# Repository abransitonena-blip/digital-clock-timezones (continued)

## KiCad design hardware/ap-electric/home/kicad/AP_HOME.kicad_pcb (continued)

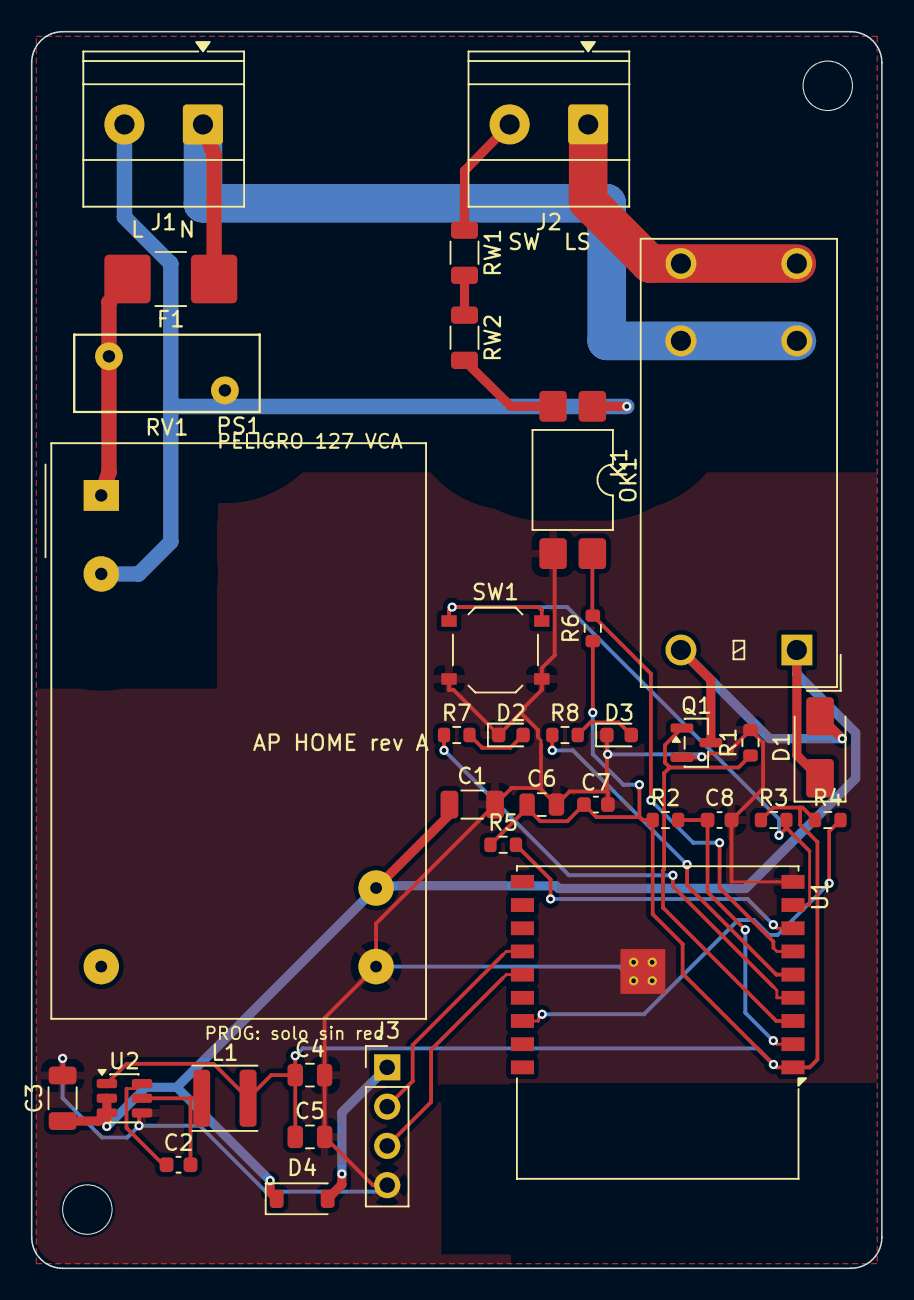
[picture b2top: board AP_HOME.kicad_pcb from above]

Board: 2 copper layers, 55.0 x 80.0 mm, 37 parts (0 on the bottom side), 26 nets.

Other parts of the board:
H1, H2: MountingHole_3.2mm_M3

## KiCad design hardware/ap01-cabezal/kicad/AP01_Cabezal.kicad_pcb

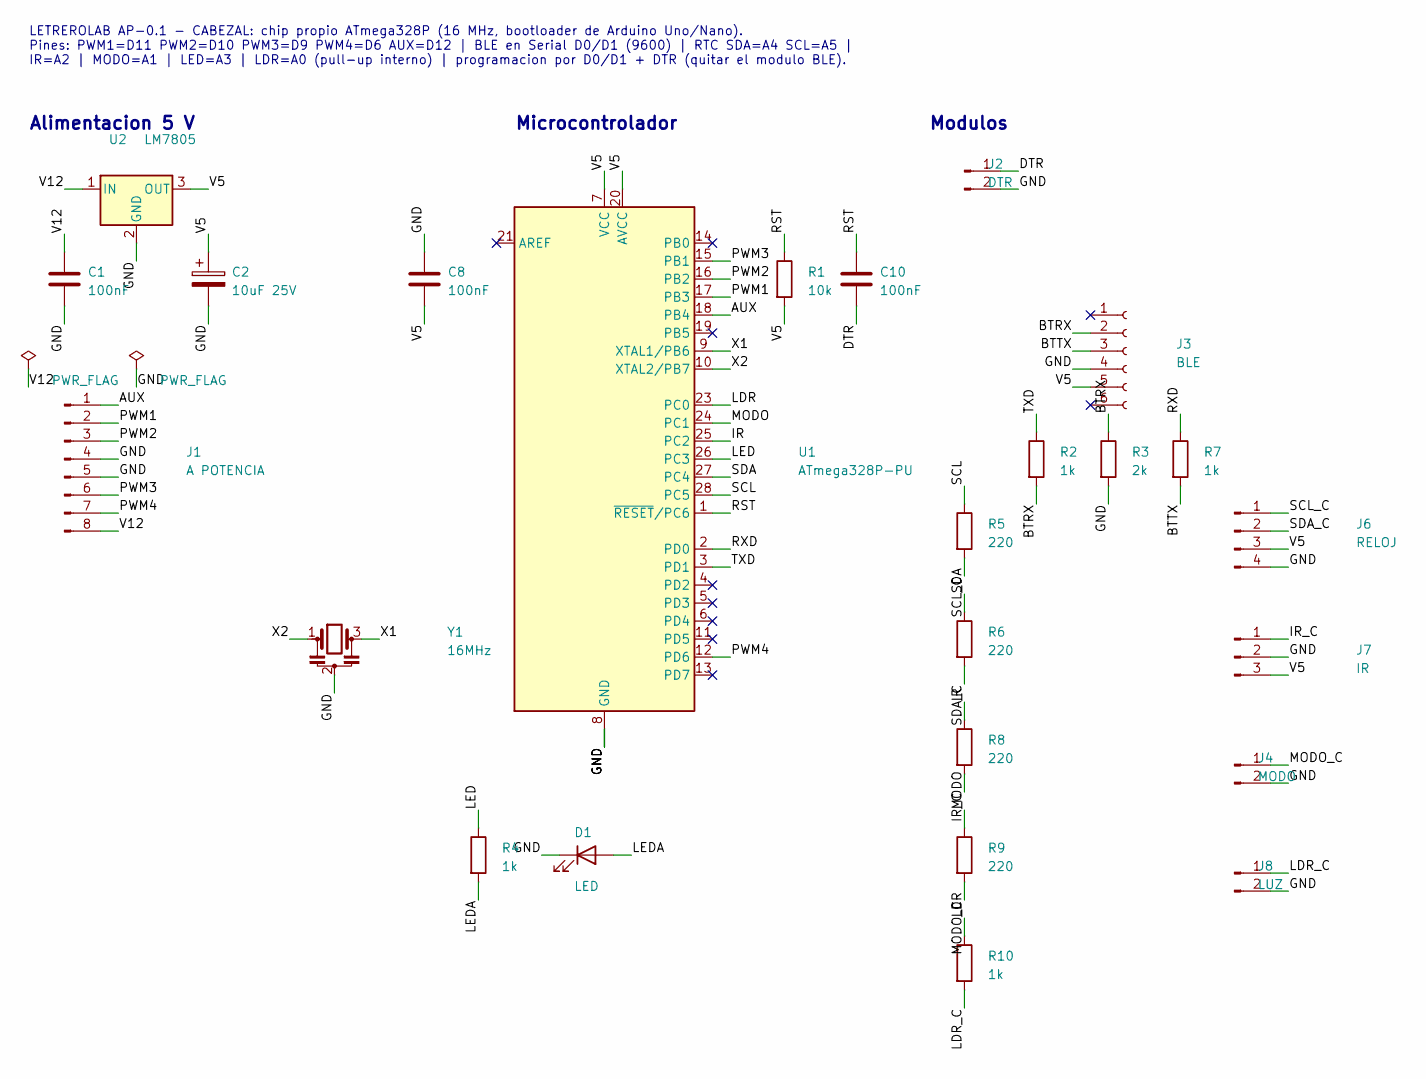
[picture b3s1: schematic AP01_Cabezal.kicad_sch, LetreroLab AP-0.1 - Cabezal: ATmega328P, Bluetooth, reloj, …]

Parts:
C1, C8: 100nF; C_Disc_P2.54mm
C2: 10uF 25V; CP_Radial_D5.0mm_P2.54mm
C10: 100nF; C_Disc_P5.08mm
D1: LED; LED_D3.0mm
J1: A POTENCIA; Pines_1x08_P2.54mm
J2: DTR; Pines_1x02_P2.54mm
J3: BLE; Zocalo_1x06_P2.54mm
J4: MODO; Pines_1x02_P2.54mm
J6: RELOJ; Pines_1x04_P2.54mm
J7: IR; Pines_1x03_P2.54mm
J8: LUZ; Pines_1x02_P2.54mm
R1: 10k; R_Vertical_P2.54mm
R2, R4, R7, R10: 1k; R_Vertical_P5.08mm
R3: 2k; R_Vertical_P5.08mm
R5, R6, R8, R9: 220; R_Vertical_P5.08mm
U1: ATmega328P-PU; DIP-28_W7.62mm
U2: LM7805; TO-220_7805
Y1: 16MHz; Resonador_3P_P2.54mm

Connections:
/AUX: J1.1, U1.18 (PB4)
/BTRX: J3.2, R2.2, R3.1
/BTTX: J3.3, R7.2
/DTR: C10.2, J2.1
/GND: C1.2, C2.2, C8.1, D1.1 (K), J1.4, J1.5, J2.2, J3.4, J4.2, J6.4, J7.2, J8.2, R3.2, U1.8 (GND), U1.22 (GND), U2.2 (GND), Y1.2
/IR: R8.1, U1.25 (PC2)
/IR_C: J7.1, R8.2
/LDR: R10.1, U1.23 (PC0)
/LDR_C: J8.1, R10.2
/LED: R4.1, U1.26 (PC3)
/LEDA: D1.2 (A), R4.2
/MODO: R9.1, U1.24 (PC1)
/MODO_C: J4.1, R9.2
/PWM1: J1.2, U1.17 (PB3)
/PWM2: J1.3, U1.16 (PB2)
/PWM3: J1.6, U1.15 (PB1)
/PWM4: J1.7, U1.12 (PD6)
/RST: C10.1, R1.1, U1.1 (~RESET/PC6)
/RXD: R7.1, U1.2 (PD0)
/SCL: R5.1, U1.28 (PC5)
/SCL_C: J6.1, R5.2
/SDA: R6.1, U1.27 (PC4)
/SDA_C: J6.2, R6.2
/TXD: R2.1, U1.3 (PD1)
/V5: C2.1, C8.2, J3.5, J6.3, J7.3, R1.2, U1.7 (VCC), U1.20 (AVCC), U2.3 (OUT)
/V12: C1.1, J1.8, U2.1 (IN)
/X1: U1.9 (XTAL1/PB6), Y1.3
/X2: U1.10 (XTAL2/PB7), Y1.1

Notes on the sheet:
LETREROLAB AP-0.1 - CABEZAL: chip propio ATmega328P (16 MHz, bootloader de Arduino Uno/Nano). Pines: PWM1=D11 PWM2=D10 PWM3=D9 PWM4=D6 AUX=D12 | BLE en Serial D0/D1 (9600) | RTC SDA=A4 SCL=A5 | IR=A2 | MODO=A1 | LED=A3 | LDR=A0 (pull-up interno) | programacion por D0/D1 + DTR (quitar el modulo BLE).
Alimentacion 5 V
Microcontrolador
Modulos

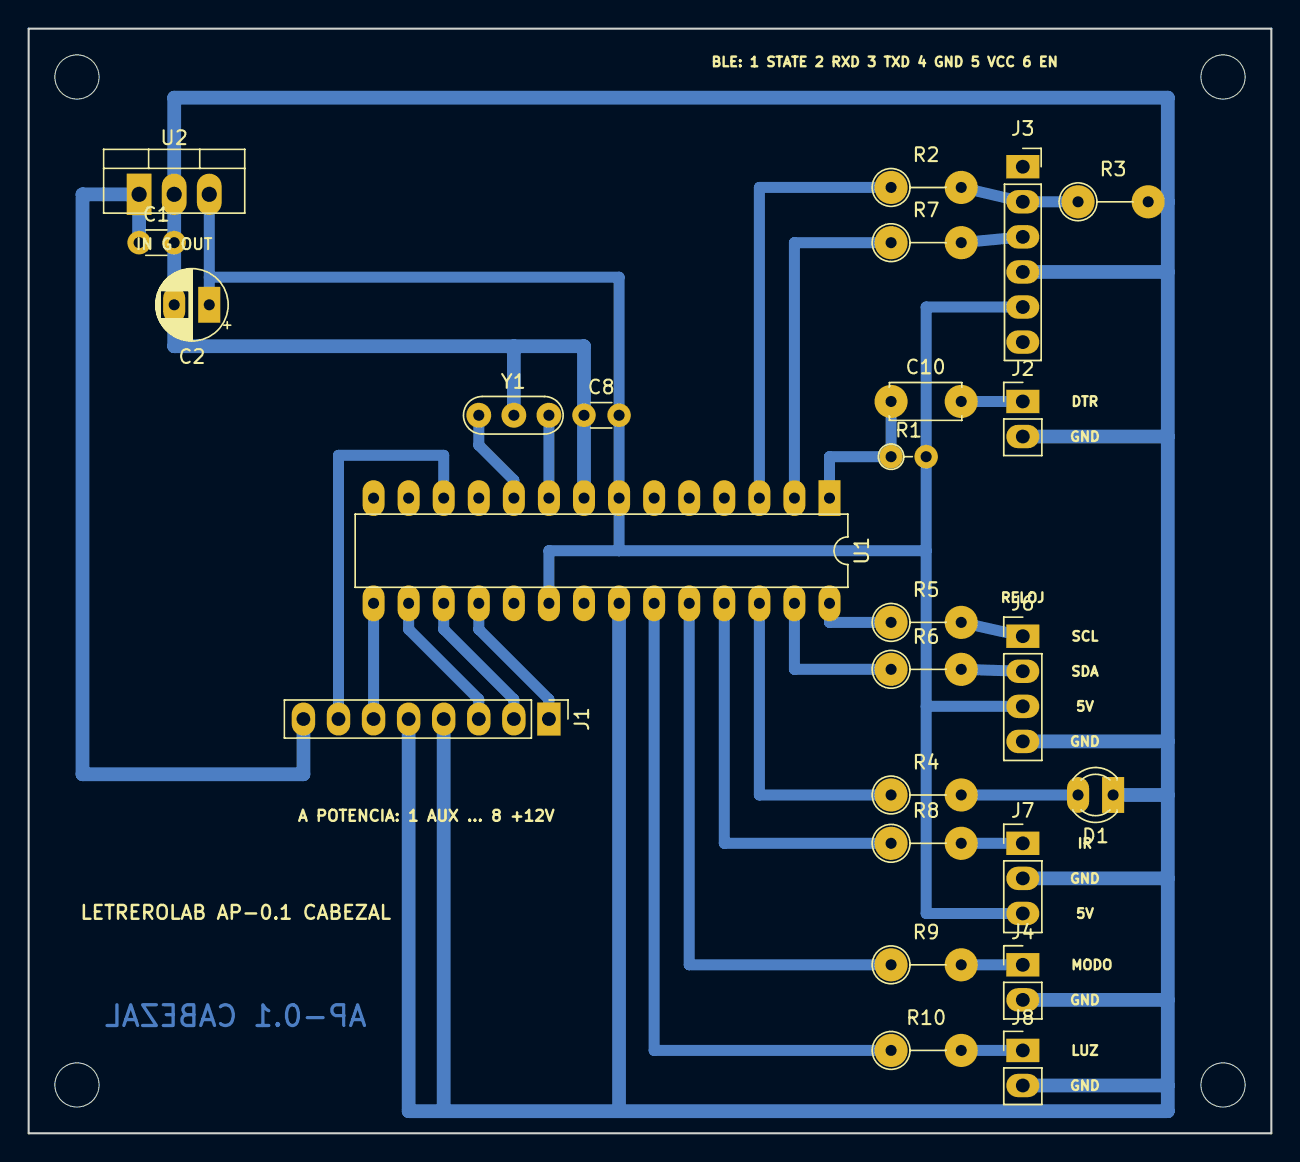
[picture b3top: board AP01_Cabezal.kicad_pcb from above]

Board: 2 copper layers, 90.0 x 80.0 mm, 29 parts (0 on the bottom side), 28 nets.

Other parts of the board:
H1, H2, H3, H4: MountingHole_3.2mm_M3; Barreno_M3_3.2mm

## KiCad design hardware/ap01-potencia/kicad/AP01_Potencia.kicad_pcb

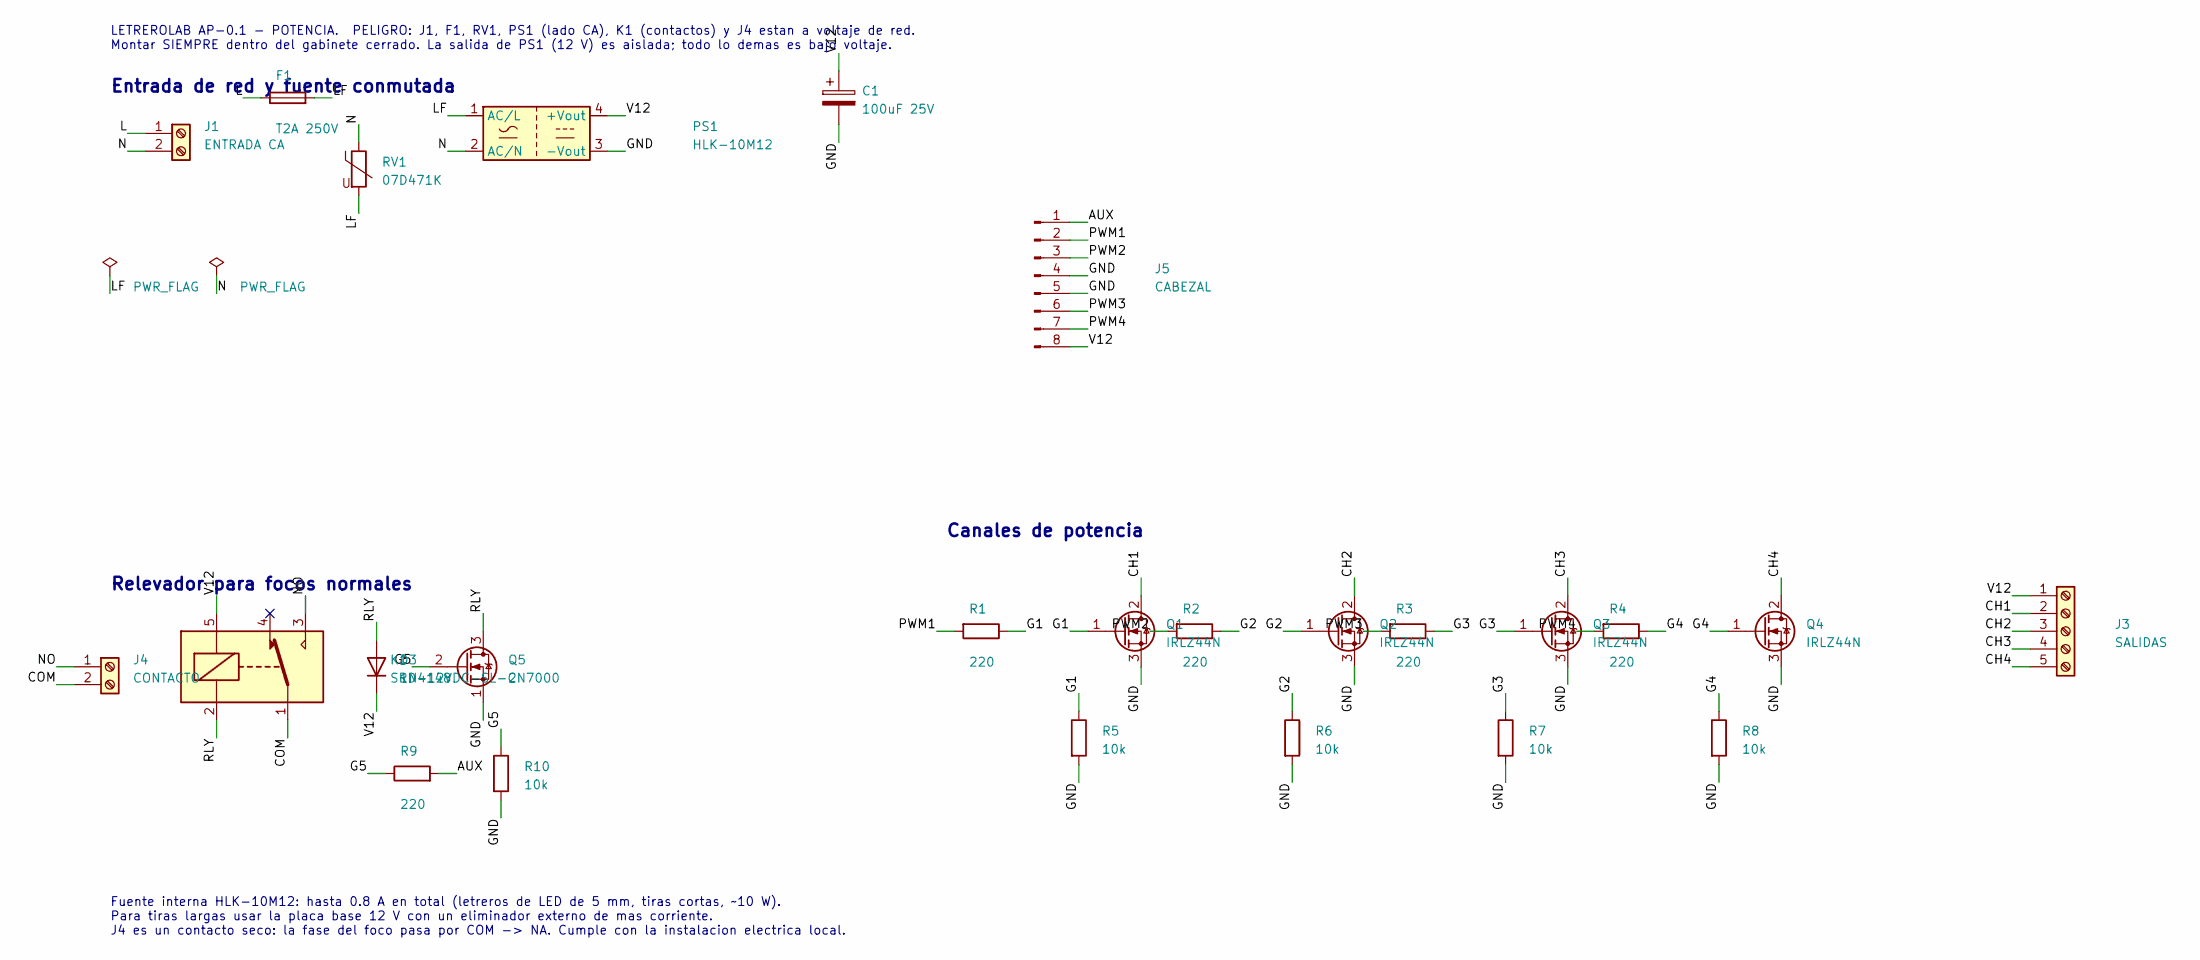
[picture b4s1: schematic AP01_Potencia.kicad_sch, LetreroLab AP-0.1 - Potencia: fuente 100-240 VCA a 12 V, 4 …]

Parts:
C1: 100uF 25V; CP_Radial_D5.0mm_P2.54mm
D3: 1N4148; D_DO-35_Vertical_P5.08mm
F1: T2A 250V; Fusible_TR5_P5.08mm
J1: ENTRADA CA; Clema_2P_P5.08mm
J3: SALIDAS; Clema_5P_P5.08mm
J4: CONTACTO; Clema_2P_P5.08mm
J5: CABEZAL; Pines_1x08_P2.54mm
K1: SRD-12VDC-SL-C; Rele_SRD_FormC
PS1: HLK-10M12; HLK-10Mxx
Q1, Q2, Q3, Q4: IRLZ44N; TO-220_MOSFET
Q5: 2N7000; TO-92_2N7000
R1, R2, R3, R4, R9: 220; R_Vertical_P5.08mm
R5, R6, R7, R8: 10k; R_Vertical_P5.08mm
R10: 10k; R_Vertical_P2.54mm
RV1: 07D471K; Varistor_D7mm_P5mm

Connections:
/AUX: J5.1, R9.2
/CH1: J3.2, Q1.2 (D)
/CH2: J3.3, Q2.2 (D)
/CH3: J3.4, Q3.2 (D)
/CH4: J3.5, Q4.2 (D)
/COM: J4.2, K1.1
/G1: Q1.1 (G), R1.1, R5.1
/G2: Q2.1 (G), R2.1, R6.1
/G3: Q3.1 (G), R3.1, R7.1
/G4: Q4.1 (G), R4.1, R8.1
/G5: Q5.2 (G), R9.1, R10.1
/GND: C1.2, J5.4, J5.5, PS1.3 (-Vout), Q1.3 (S), Q2.3 (S), Q3.3 (S), Q4.3 (S), Q5.1 (S), R5.2, R6.2, R7.2, R8.2, R10.2
/L: F1.1, J1.1
/LF: F1.2, PS1.1 (AC/L), RV1.2
/N: J1.2, PS1.2 (AC/N), RV1.1
/NO: J4.1, K1.3
/PWM1: J5.2, R1.2
/PWM2: J5.3, R2.2
/PWM3: J5.6, R3.2
/PWM4: J5.7, R4.2
/RLY: D3.2 (A), K1.2, Q5.3 (D)
/V12: C1.1, D3.1 (K), J3.1, J5.8, K1.5, PS1.4 (+Vout)

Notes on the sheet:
LETREROLAB AP-0.1 - POTENCIA. PELIGRO: J1, F1, RV1, PS1 (lado CA), K1 (contactos) y J4 estan a voltaje de red. Montar SIEMPRE dentro del gabinete cerrado. La salida de PS1 (12 V) es aislada; todo lo demas es bajo voltaje.
Fuente interna HLK-10M12: hasta 0.8 A en total (letreros de LED de 5 mm, tiras cortas, ~10 W). Para tiras largas usar la placa base 12 V con un eliminador externo de mas corriente. J4 es un contacto seco: la fase del foco pasa por COM -> NA. Cumple con la instalacion electrica local.
Entrada de red y fuente conmutada
Relevador para focos normales
Canales de potencia

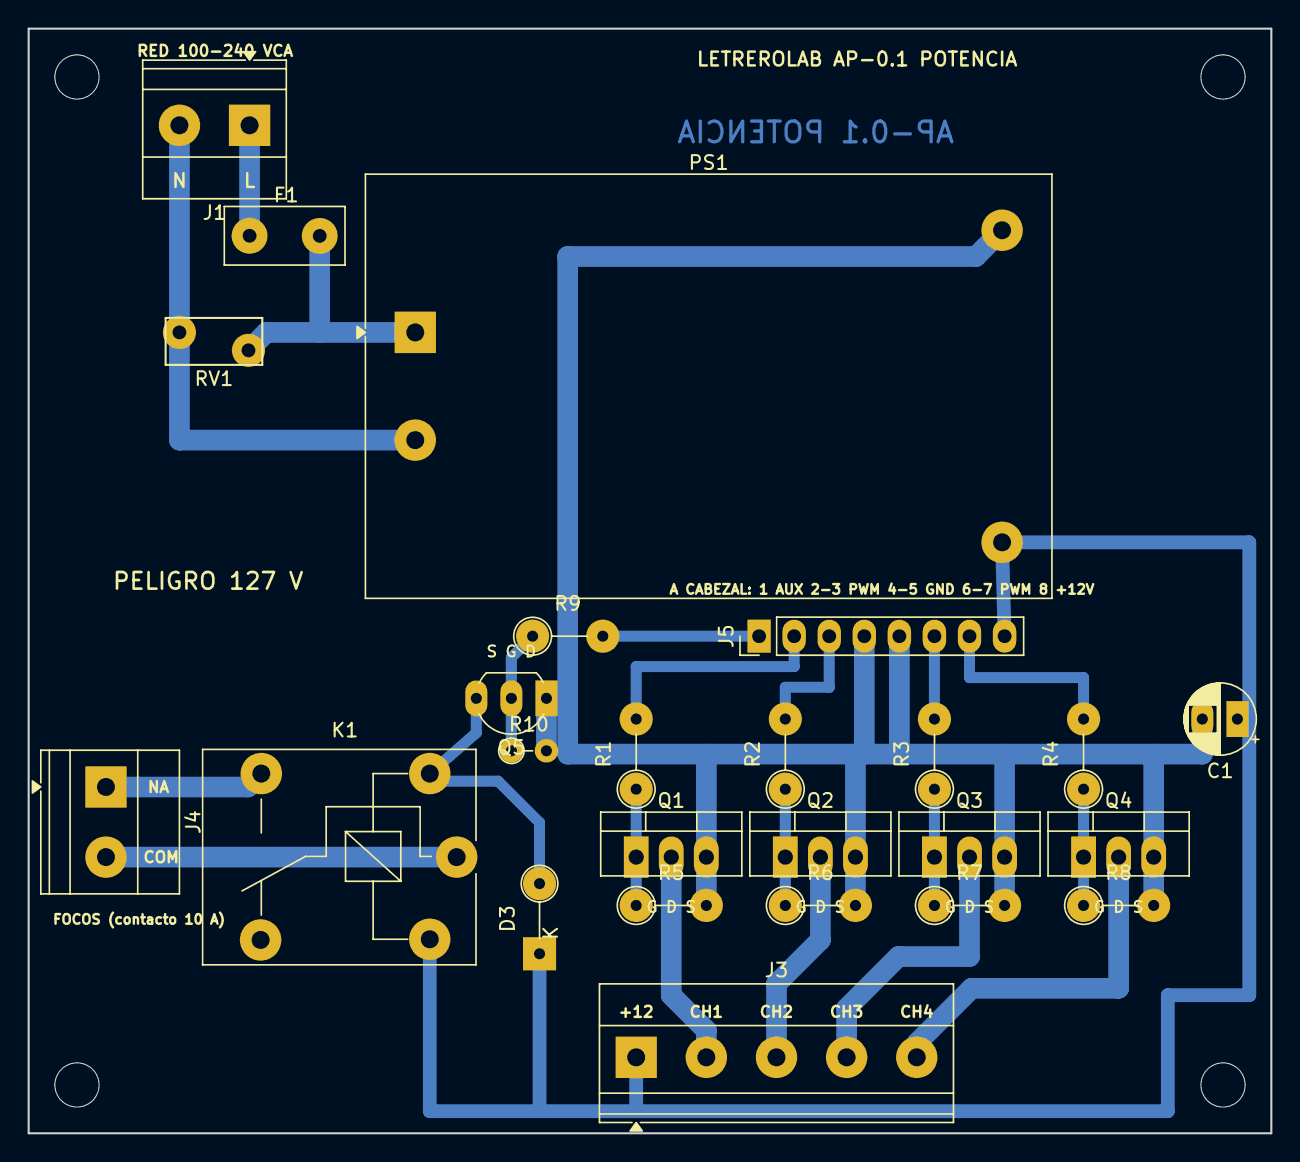
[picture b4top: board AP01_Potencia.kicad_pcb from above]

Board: 2 copper layers, 90.0 x 80.0 mm, 29 parts (0 on the bottom side), 22 nets.

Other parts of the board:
H1, H2, H3, H4: MountingHole_3.2mm_M3; Barreno_M3_3.2mm

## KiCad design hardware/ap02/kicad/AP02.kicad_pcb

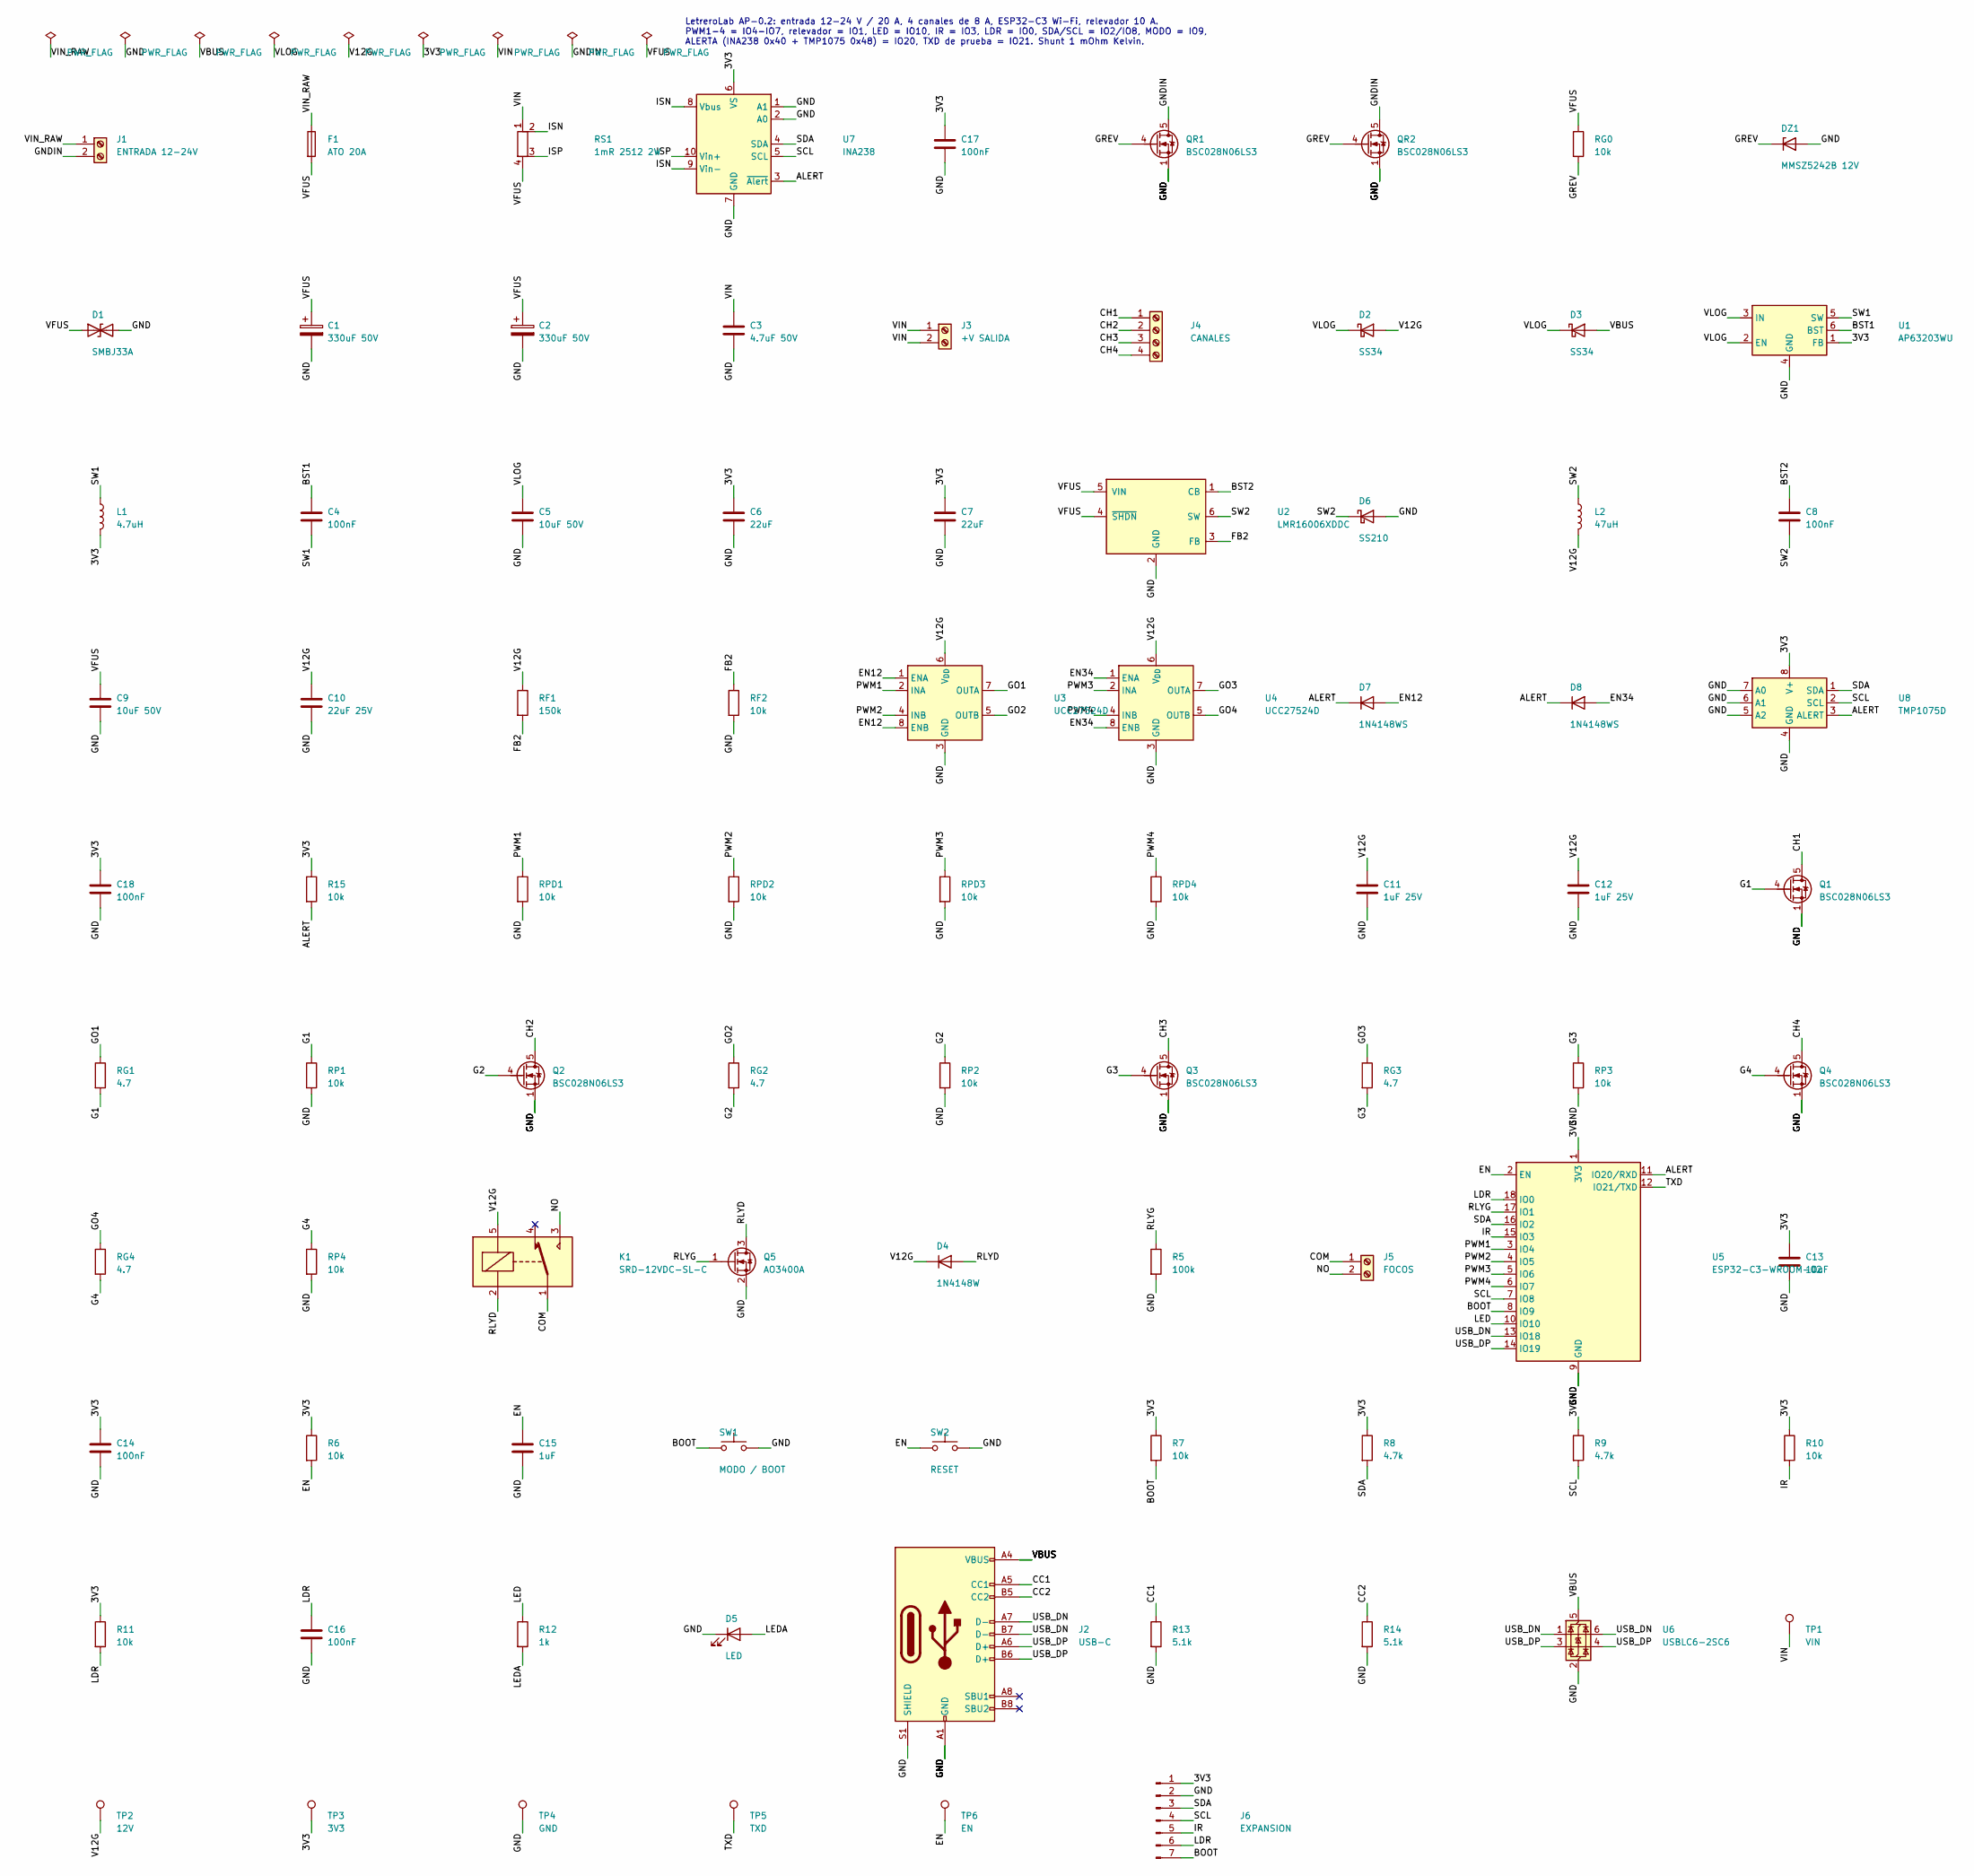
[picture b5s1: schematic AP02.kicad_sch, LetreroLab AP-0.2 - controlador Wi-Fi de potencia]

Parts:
C1, C2: 330uF 50V; CP_Elec_10x10.5
C3: 4.7uF 50V; C_1206_3216Metric
C4, C8, C14, C16, C17, C18: 100nF; C_0603_1608Metric
C5, C9: 10uF 50V; C_1206_3216Metric
C6, C7: 22uF; C_0805_2012Metric
C10: 22uF 25V; C_1206_3216Metric
C11, C12: 1uF 25V; C_0603_1608Metric
C13: 10uF; C_0805_2012Metric
C15: 1uF; C_0603_1608Metric
D1: SMBJ33A; D_SMB
D2, D3: SS34; D_SMA
D4: 1N4148W; D_SOD-123
D5: LED; LED_0603_1608Metric
D6: SS210; D_SMA
D7, D8: 1N4148WS; D_SOD-323
DZ1: MMSZ5242B 12V; D_SOD-123
F1: ATO 20A; Fuseholder_Blade_ATO_Littelfuse_Pudenz_2_Pin
J1: ENTRADA 12-24V; TerminalBlock_Phoenix_MKDS-3-2-5.08_1x02_P5.08mm_Horizontal
J2: USB-C; USB_C_Receptacle_HRO_TYPE-C-31-M-12
J3: +V SALIDA; TerminalBlock_Phoenix_MKDS-3-2-5.08_1x02_P5.08mm_Horizontal
J4: CANALES; TerminalBlock_Phoenix_MKDS-3-4-5.08_1x04_P5.08mm_Horizontal
J5: FOCOS; TerminalBlock_Phoenix_MKDS-1,5-2-5.08_1x02_P5.08mm_Horizont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
J6: EXPANSION; PinHeader_1x07_P2.54mm_Vertical
K1: SRD-12VDC-SL-C; Relay_SPDT_SANYOU_SRD_Series_Form_C
L1: 4.7uH; L_Changjiang_FNR4030S
L2: 47uH; L_Changjiang_FNR4030S
Q1, Q2, Q3, Q4: BSC028N06LS3; TDSON-8-1
Q5: AO3400A; SOT-23
QR1, QR2: BSC028N06LS3; TDSON-8-1
R5: 100k; R_0603_1608Metric
R6, R7, R10, R11, R15: 10k; R_0603_1608Metric
R8, R9: 4.7k; R_0603_1608Metric
R12: 1k; R_0603_1608Metric
R13, R14: 5.1k; R_0603_1608Metric
RF1: 150k; R_0603_1608Metric
RF2: 10k; R_0603_1608Metric
RG0: 10k; R_0603_1608Metric
RG1, RG2, RG3, RG4: 4.7; R_0603_1608Metric
RP1, RP2, RP3, RP4: 10k; R_0603_1608Metric
RPD1, RPD2, RPD3, RPD4: 10k; R_0603_1608Metric
RS1: 1mR 2512 2W; R_2512_Kelvin_NetTie
SW1: MODO / BOOT; SW_Push_1P1T_XKB_TS-1187A
SW2: RESET; SW_Push_1P1T_XKB_TS-1187A
TP1: VIN; TestPoint_Pad_D1.5mm
TP2: 12V; TestPoint_Pad_D1.5mm
TP3: 3V3; TestPoint_Pad_D1.5mm
TP4: GND; TestPoint_Pad_D1.5mm
TP5: TXD; TestPoint_Pad_D1.5mm
TP6: EN; TestPoint_Pad_D1.5mm
U1: AP63203WU; TSOT-23-6
U2: LMR16006XDDC; SOT-23-6
U3, U4: UCC27524D; SOIC-8_3.9x4.9mm_P1.27mm
U5: ESP32-C3-WROOM-02; ESP32-C3-WROOM-02_JLC
U6: USBLC6-2SC6; SOT-23-6
U7: INA238; VSSOP-10_3x3mm_P0.5mm
U8: TMP1075D; SOIC-8_3.9x4.9mm_P1.27mm

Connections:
/3V3: C6.1, C7.1, C13.1, C14.1, C17.1, C18.1, J6.1, L1.2, R6.1, R7.1, R8.1, R9.1, R10.1, R11.1, R15.1, TP3.1, U1.1 (FB), U5.1 (3V3), U7.6 (VS), U8.8 (V+)
/ALERT: D7.1 (K), D8.1 (K), R15.2, U5.11 (IO20/RXD), U7.3 (~Alert), U8.3 (ALERT)
/BOOT: J6.7, R7.2, SW1.1, U5.8 (IO9)
/BST1: C4.1, U1.6 (BST)
/BST2: C8.1, U2.1 (CB)
/CC1: J2.A5 (CC1), R13.1
/CC2: J2.B5 (CC2), R14.1
/CH1: J4.1, Q1.5 (D)
/CH2: J4.2, Q2.5 (D)
/CH3: J4.3, Q3.5 (D)
/CH4: J4.4, Q4.5 (D)
/COM: J5.1, K1.1
/EN: C15.1, R6.2, SW2.1, TP6.1, U5.2 (EN)
/EN12: D7.2 (A), U3.1 (ENA), U3.8 (ENB)
/EN34: D8.2 (A), U4.1 (ENA), U4.8 (ENB)
/FB2: RF1.2, RF2.1, U2.3 (FB)
/G1: Q1.4 (G), RG1.2, RP1.1
/G2: Q2.4 (G), RG2.2, RP2.1
/G3: Q3.4 (G), RG3.2, RP3.1
/G4: Q4.4 (G), RG4.2, RP4.1
/GND: C1.2, C2.2, C3.2, C5.2, C6.2, C7.2, C9.2, C10.2, C11.2, C12.2, C13.2, C14.2, C15.2, C16.2, C17.2, C18.2, D1.2 (A2), D5.1 (K), D6.2 (A), DZ1.2 (A), J2.A1 (GND), J2.A12 (GND), J2.B1 (GND), J2.B12 (GND), J2.S1 (SHIELD), J6.2, Q1.1 (S), Q1.2 (S), Q1.3 (S), Q2.1 (S), Q2.2 (S), Q2.3 (S), Q3.1 (S), Q3.2 (S), Q3.3 (S), Q4.1 (S), Q4.2 (S), Q4.3 (S), Q5.2 (S), QR1.1 (S), QR1.2 (S), QR1.3 (S), QR2.1 (S), QR2.2 (S), QR2.3 (S), R5.2, R13.2, R14.2, RF2.2, RP1.2, RP2.2, RP3.2, RP4.2, RPD1.2, RPD2.2, RPD3.2, RPD4.2, SW1.2, SW2.2, TP4.1, U1.4 (GND), U2.2 (GND), U3.3 (GND), U4.3 (GND), U5.9 (GND), U5.19 (GND), U6.2 (GND), U7.1 (A1), U7.2 (A0), U7.7 (GND), U8.4 (GND), U8.5 (A2), U8.6 (A1), U8.7 (A0)
/GNDIN: J1.2, QR1.5 (D), QR2.5 (D)
/GO1: RG1.1, U3.7 (OUTA)
/GO2: RG2.1, U3.5 (OUTB)
/GO3: RG3.1, U4.7 (OUTA)
/GO4: RG4.1, U4.5 (OUTB)
/GREV: DZ1.1 (K), QR1.4 (G), QR2.4 (G), RG0.2
/IR: J6.5, R10.2, U5.15 (IO3)
/ISN: RS1.2, U7.8 (Vbus), U7.9 (Vin-)
/ISP: RS1.3, U7.10 (Vin+)
/LDR: C16.1, J6.6, R11.2, U5.18 (IO0)
/LED: R12.1, U5.10 (IO10)
/LEDA: D5.2 (A), R12.2
/NO: J5.2, K1.3
/PWM1: RPD1.1, U3.2 (INA), U5.3 (IO4)
/PWM2: RPD2.1, U3.4 (INB), U5.4 (IO5)
/PWM3: RPD3.1, U4.2 (INA), U5.5 (IO6)
/PWM4: RPD4.1, U4.4 (INB), U5.6 (IO7)
/RLYD: D4.2 (A), K1.2, Q5.3 (D)
/RLYG: Q5.1 (G), R5.1, U5.17 (IO1)
/SCL: J6.4, R9.2, U5.7 (IO8), U7.5 (SCL), U8.2 (SCL)
/SDA: J6.3, R8.2, U5.16 (IO2), U7.4 (SDA), U8.1 (SDA)
/SW1: C4.2, L1.1, U1.5 (SW)
/SW2: C8.2, D6.1 (K), L2.1, U2.6 (SW)
/TXD: TP5.1, U5.12 (IO21/TXD)
/USB_DN: J2.A7 (D-), J2.B7 (D-), U5.13 (IO18), U6.1 (I/O1), U6.6 (I/O1)
/USB_DP: J2.A6 (D+), J2.B6 (D+), U5.14 (IO19), U6.3 (I/O2), U6.4 (I/O2)
/V12G: C10.1, C11.1, C12.1, D2.2 (A), D4.1 (K), K1.5, L2.2, RF1.1, TP2.1, U3.6 (V_{DD}), U4.6 (V_{DD})
/VBUS: D3.2 (A), J2.A4 (VBUS), J2.A9 (VBUS), J2.B4 (VBUS), J2.B9 (VBUS), U6.5 (VBUS)
/VFUS: C1.1, C2.1, C9.1, D1.1 (A1), F1.2, RG0.1, RS1.4, U2.4 (~SHDN), U2.5 (VIN)
/VIN: C3.1, J3.1, J3.2, RS1.1, TP1.1
/VIN_RAW: F1.1, J1.1
/VLOG: C5.1, D2.1 (K), D3.1 (K), U1.2 (EN), U1.3 (IN)

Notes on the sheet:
LetreroLab AP-0.2: entrada 12-24 V / 20 A, 4 canales de 8 A, ESP32-C3 Wi-Fi, relevador 10 A. PWM1-4 = IO4-IO7, relevador = IO1, LED = IO10, IR = IO3, LDR = IO0, SDA/SCL = IO2/IO8, MODO = IO9, ALERTA (INA238 0x40 + TMP1075 0x48) = IO20, TXD de prueba = IO21. Shunt 1 mOhm Kelvin.

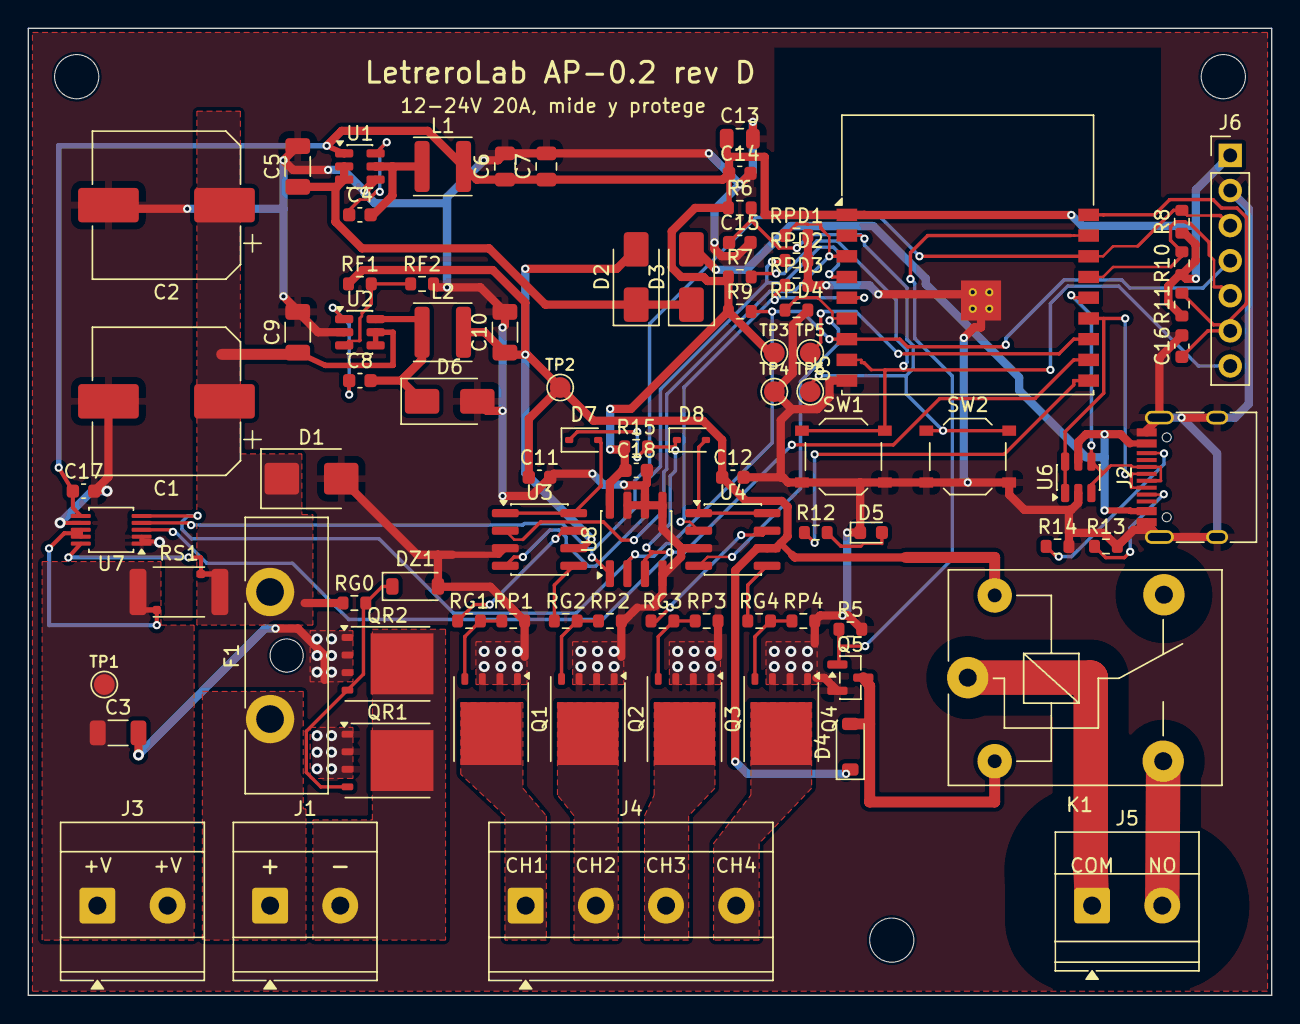
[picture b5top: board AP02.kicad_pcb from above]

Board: 2 copper layers, 90.0 x 70.0 mm, 90 parts (0 on the bottom side), 53 nets.

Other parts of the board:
H1, H2, H3: MountingHole_3.2mm_M3
